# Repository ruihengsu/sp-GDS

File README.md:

# Ray's Design Library

## What will you find?
1. A KLayout `p-cell` library - written in Python - of photolithography utilities
2. PCB Board Design Files
3. Devices Layout
4. Layouts used for past fabrication runs

## Naming Convention
All the files the library follows a specific naming convention consisting of 5 descriptors separated by a single underscore.

|# |Descriptor   | Example   |
|---|---|---|
|1| Start with your initials  | RS  |
|2| The main project that the design is relevant for  | GaAs, RC, MISC,...  |
|3| The name of the design   | EtchTest, Mesa, Hallbar, ...  |
|4| The design dimension, in mm  | 6x7, 6x6, W4in, NA...  |
|5| The date, in MMDDYY  | October 15, 2021 represented as 101521  |

Every project in the library is given a 2 to 4 alphabet code. 
| Project  | Code  |
|---|---|
| Ohmic contacts to 2DES in GaAs heterostructures | [2DEG](#2deg) |
| Distributed broadband filter on Si | [RC](#rc) |
| Other Designs (utilities, test patterns) | [MISC](#misc) |

## 2DEG

| Filename | Description | Preview |
|---|---| --- |
| `RS_2DEG_Hallbar+OhmicsTest_6x6_101821`  | Four hall bar mesas + ohmic contacts. In addition to the hall bars, there are also plenty of free ohmic contacts that can be used for testing. |  |
| `RS_2DEG_OhmicsTest_6x6_102621.GDS` | 140 um ohmic contacts with 140 um spacing, spammed onto 6 mm by 6 mm chip | |

## RC

## MISC

| Filename | Description | Preview |
|---|---|---|
| `RS_MISC_TLMEtchTest_6x6_101821`  | 300 um squares with spacing equal to 100, 200, 300, 400, 500, 600, 700 um.  | |
| `RS_MISC_TLMTemplate_NA_101821`  | 2.2 mm long rectangular mesa, with square Ohmic contacts forming a grid. | |
| `RS_MISC_EtchTest_5x5_101821`  | Etch test involving a variety of squares, circles, and test patterns.  | |
| `RS_MISC_EtchTestFlattened_5x5_101821` | Identical to `RS_MISC_EtchTest_5x5_101821`, but all PCells are flattened and merged together | |
| `RS_MISC_LineEtchTest_6x6_081821`  | Rows of vertical lines with varying thicknesses. Each line has a label indicating its thickness.  | |

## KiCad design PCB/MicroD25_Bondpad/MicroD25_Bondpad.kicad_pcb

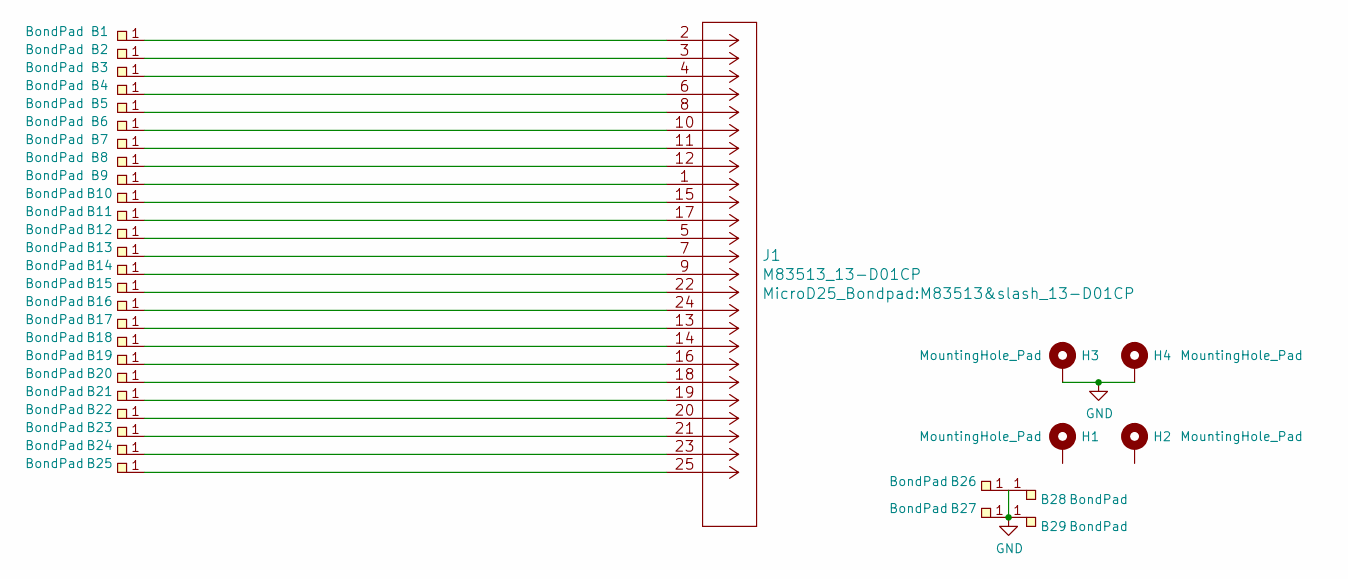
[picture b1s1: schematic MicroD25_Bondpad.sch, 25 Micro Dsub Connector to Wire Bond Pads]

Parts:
B1, B2, B3, B4, B5, B6, B7, B8, B9, B10, B11, B12, B13, B14, B15, B16, B17, B18, B19, B20, B21, B22, B23, B24, B25, B26, B27: BondPad
B28, B29: BondPad; BondPad_B.Cu
H1, H2: MountingHole_Pad; BondableMountHole
H3, H4: MountingHole_Pad; ToGND
J1: M83513_13-D01CP; M83513&slash_13-D01CP

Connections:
GND: B26.1, B27.1, B28.1, B29.1, H3.1, H4.1
unnamed: B1.1, J1.2
unnamed: B2.1, J1.3
unnamed: B3.1, J1.4
unnamed: B4.1, J1.6
unnamed: B5.1, J1.8
unnamed: B6.1, J1.10
unnamed: B7.1, J1.11
unnamed: B8.1, J1.12
unnamed: B9.1, J1.1
unnamed: B10.1, J1.15
unnamed: B11.1, J1.17
unnamed: B12.1, J1.5
unnamed: B13.1, J1.7
unnamed: B14.1, J1.9
unnamed: B15.1, J1.22
unnamed: B16.1, J1.24
unnamed: B17.1, J1.13
unnamed: B18.1, J1.14
unnamed: B19.1, J1.16
unnamed: B20.1, J1.18
unnamed: B21.1, J1.19
unnamed: B22.1, J1.20
unnamed: B23.1, J1.21
unnamed: B24.1, J1.23
unnamed: B25.1, J1.25

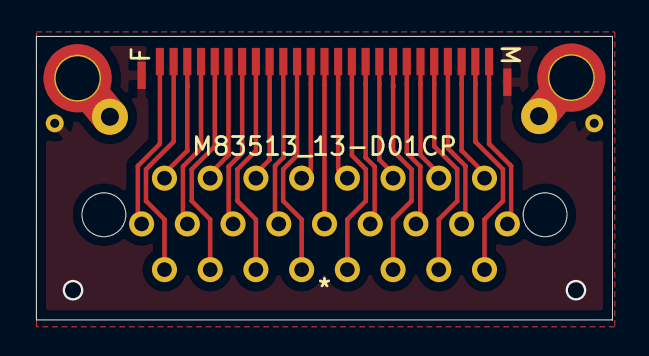
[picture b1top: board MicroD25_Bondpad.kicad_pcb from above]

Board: 2 copper layers, 32.0 x 15.7 mm, 34 parts (0 on the bottom side), 26 nets.

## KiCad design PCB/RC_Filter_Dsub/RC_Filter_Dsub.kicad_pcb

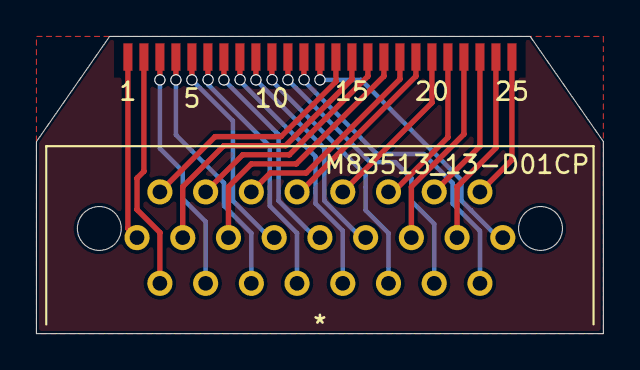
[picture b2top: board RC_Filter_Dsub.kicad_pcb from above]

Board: 2 copper layers, 31.5 x 16.5 mm, 27 parts (0 on the bottom side), 25 nets.

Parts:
1, 5, 10, 15, 20, 25: BondPad
J1: M83513_13-D01CP; M83513&slash_13-D01CP
U2, U3, U4, U6, U7, U8, U9, U11, U12, U13, U14, U16, U17, U18, U19, U21, U22, U23, U24: BondPad
U26: logo; sillyPhotons

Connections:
unnamed: 1.1, J1.1
unnamed: J1.2, U2.1
unnamed: J1.3, U3.1
unnamed: J1.4, U4.1
unnamed: 5.1, J1.5
unnamed: J1.6, U6.1
unnamed: J1.7, U7.1
unnamed: J1.8, U8.1
unnamed: J1.9, U9.1
unnamed: 10.1, J1.10
unnamed: J1.11, U11.1
unnamed: J1.12, U12.1
unnamed: J1.13, U13.1
unnamed: J1.14, U14.1
unnamed: 15.1, J1.15
unnamed: J1.16, U16.1
unnamed: J1.17, U17.1
unnamed: J1.18, U18.1
unnamed: J1.19, U19.1
unnamed: 20.1, J1.20
unnamed: J1.21, U21.1
unnamed: J1.22, U22.1
unnamed: J1.23, U23.1
unnamed: J1.24, U24.1
unnamed: 25.1, J1.25

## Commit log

2021-07-19 Good
2021-07-23 Great!
2021-07-28 Made ohmics over lap with mesa!
2021-07-28 Good stuff mate
2021-07-28 Modified the etch calibration file
2021-07-28 Good stuff
2021-08-01 Started working on alignment marks with coordinates
2021-08-02 Added 2 by 2 chip
2021-08-03 Made the 50 um square on the ohmics layer further a part from each other.
2021-08-03 Prettified the macro file.
2021-08-03 Small updates
2021-08-24 Updated Directory Structure
2021-09-08 Great
2021-09-22 GreatGreat
2021-10-05 Great. Updated my macros library
2021-10-05 RC Test Wafer Design With Mario's Suggestion
2021-10-05 Updated the subcell for leak test
2021-10-20 Okay
2021-10-27 GreatGrea
2021-11-15 Push
2022-07-05 Finally update

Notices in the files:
parts and their libraries:
Copyright 2021 Accelerated Designs. All rights reserved.
